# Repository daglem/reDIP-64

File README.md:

# reDIP 64

## Commodore 64 FPGA emulation platform

## Overview

The reDIP 64 is an open source hardware development board which
combines the following in a tiny 25.40 x 50.80 mm footprint:

* Lattice ECP5-5G FPGA (LFE5UM5G-25)
* NXP PTN5110NHQ USB PD TCPC PHY
* NXP SGTL5000 Audio Codec
* 128Mbit FLASH
* 128Mbit HyperRAM
* RGB LED
* Push button
* USB-C receptacle for power, Full Speed USB, and DisplayPort (DP Alt Mode)
* Lots of 5V tolerant I/O

The reDIP 64 aims at functioning as

* A partial or full brain transplant for the venerable Commodore 64
* A "Retro computer on a chip", which can be used stand-alone or in
  custom retro computer builds
* A versatile generic FPGA platform with power, HID input, and audio /
  video output all handled through a single USB-C connector

Designs for the ECP5 FPGA can be processed by
[yosys](https://github.com/YosysHQ/yosys/) and
[nextpnr](https://github.com/YosysHQ/nextpnr/).

Also check out the [reDIP SID](https://github.com/daglem/reDIP-SID),
if you are interested in a platform for MOS 6581 / 8580 SID emulation
in particular.

## General use

### I/O interfaces

#### 100 header pins:

* 5V input / output
* 3.3V output
* 92 FPGA GPIO
* 5 audio pins (stereo line input, stereo line output, GND)
* GND

All FPGA I/O is 5V tolerant, and can drive 5V TTL.

Note that the audio line inputs are not AC coupled - AC coupling must
be externally added for audio applications. Without external AC
coupling, the line inputs can conceivably be used as generic ADCs.

#### JTAG:

A separate 6 pin header is provided for JTAG.

#### USB-C functions:

* 5V power in / out
* USB Power Delivery (PD)
* FPGA Full Speed USB
* FPGA DisplayPort (DP Alt Mode)

## Commodore 64 compatibility

The board is pin compatible with the MOS 6510 / 8500 MPU chip, and has
additional pin headers to cover all the custom chips and I/O in the
Commodore 64:

* 6510 / 8500 MPU
* 6567/6569 / 8562/8565 VIC-II
* 6581 / 8580 SID (x 2)
* 2 x 6526 CIA
* Cartridge port signals
* Menu / freeze button

For anyone interested in experimenting with a Commodore 64 setup,
while avoiding blown fuses and a broken reDIP 64 board:

* A 2A C64 power supply is recommended
* Be careful not to apply force to SMD components on insertion and removal - use a ZIF socket if possible

The idea is that one can start by mounting the reDIP 64 in a Commodore
64, replacing the 6510 / 8500 MPU. This will make it possible to communicate
with the Commodore 64 via USB, to output audio and video via the USB-C
connector (DP Alt Mode), and to emulate a second SID chip.

Then, if one wishes to replace the VIC-II, the SID, or a CIA chip, the
custom chip is removed, and wires are run from the reDIP 64 to the
corresponding socket pins for the custom chip.

Note that the audio line outputs cannot drive the C64 audio output
stage directly, however an audio output may be connected directly to
pin 3 of the C64 audio/video connector (preferably removing or cutting
a pin on C13 in the C64).

Also note that unless suggested GPIO is repurposed for other
functions, the VIC-II can only be replaced by additionally emulating
all RAM chips, and the PLA can only be replaced by emulating *all*
custom chips, including ROM and RAM.

The MOS 8502 MPU used in the Commodore C128 has a similar pinout to
the MOS 6510. Since the same pins are used for power, the reDIP 64 can
conceivably also be used in a C128.

## Retro computer on a chip

Power, HID input, and audio / video can all be handled via the USB-C
port, hence the reDIP 64 is in fact capable of operating as a retro
computer all on its own. Just connect the reDIP 64 to a DisplayPort
monitor, either directly or via an USB hub, and add a keyboard and any
other HID input devices. Now, all that is needed is an FPGA
implementation of a retro computer :wink:

To create a fully functional retro computer, i.e. with I/O which can
interface with original perhiperals, physical connectors and glue
logic must be added to the mix. This can make for some fun projects!

Using the suggested GPIO, a fully functional custom C64 can be built
using a minimum of additional components.

## Other FPGA projects

The board can be of course also be used to experiment with e.g.

* DisplayPort audio / video
* Analog audio
* USB Power Delivery
* Interfacing with 5V TTL
* RISC-V and other CPU architectures
* Other SoC projects

## Disclaimer

Please note that this is only my third board design - rookie mistakes
are probably made, and feedback is welcome.

## Board images

Board Front | Board Back
----------- | ----------
 |

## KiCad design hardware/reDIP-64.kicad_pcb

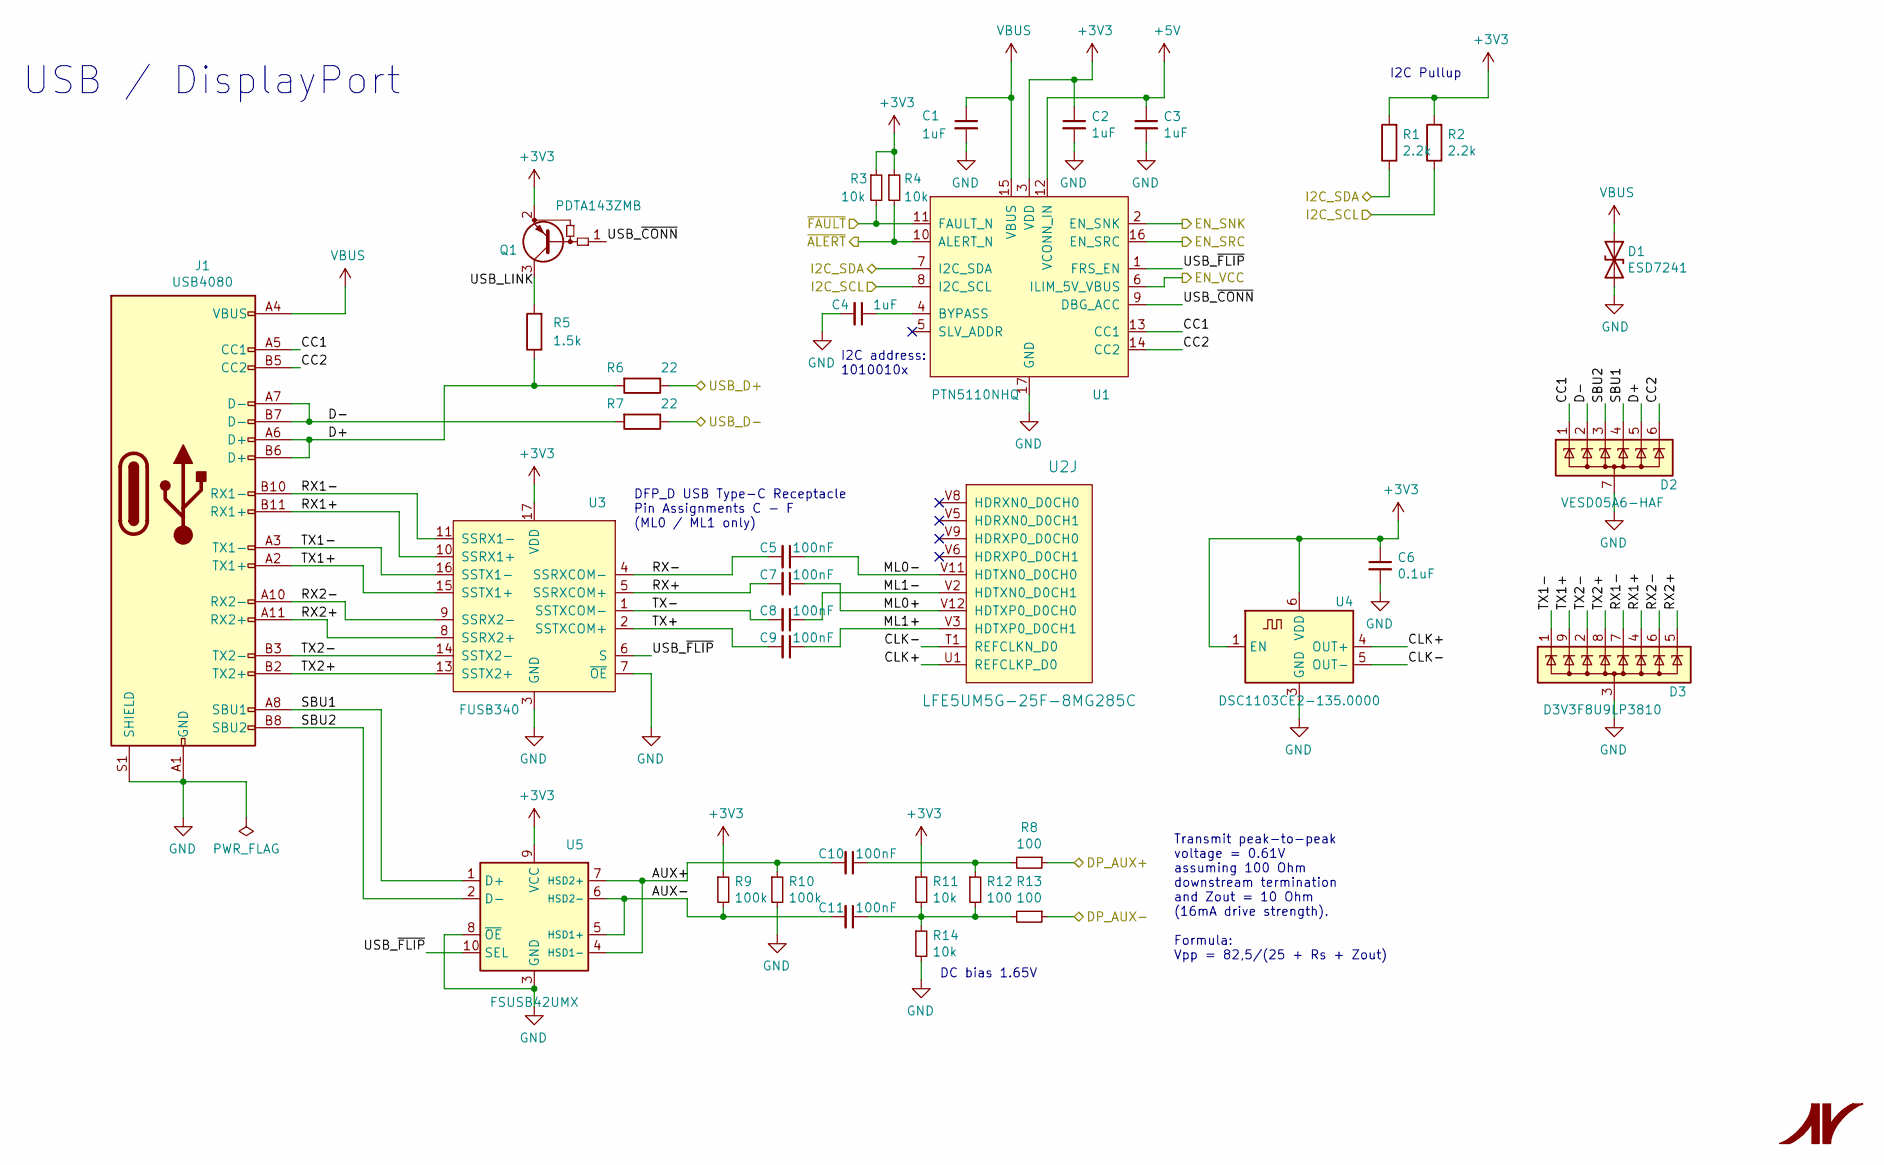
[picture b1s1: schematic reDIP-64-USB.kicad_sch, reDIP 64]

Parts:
C1: 1uF; C_0402_1005Metric
C2, C3, C4: 1uF; C_0201_0603Metric
C5, C7, C8, C9, C10, C11: 100nF; C_0201_0603Metric
C6: 0.1uF; C_0201_0603Metric
D1: ESD7241; CASE_714AB_1.0x0.6mm
D2: VESD05A6-HAF; LLP75-7L
D3: D3V3F8U9LP3810; U-DFN3810-9
J1: USB4080; USB_C_Receptacle_GCT_USB4080
Q1: PDTA143ZMB; SOT-883
R1, R2: 2.2k; R_0201_0603Metric
R3, R4, R11, R14: 10k; R_0201_0603Metric
R5: 1.5k; R_0201_0603Metric
R6, R7: 22; R_0201_0603Metric
R8, R12, R13: 100; R_0201_0603Metric
R9, R10: 100k; R_0201_0603Metric
U1: PTN5110NHQ; SOT-1883-1
U2: LFE5UM5G-25F-8MG285C; BGA-285_10x10mm_P0.5mm
U3: FUSB340; CASE_722AB_2.0x2.8mm_P0.4mm
U4: DSC1103CE2-135.0000; Oscillator_SMD_3225-6Pin_3.2x2.5mm
U5: FSUSB42UMX; CASE_523BC_1.4x1.8_P0.4mm

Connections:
+3V3: C2.1, C6.1, Q1.2 (E), R1.2, R2.2, R3.1, R4.1, R9.1, R11.1, U1.3 (VDD), U3.17 (VDD), U4.1 (EN), U4.6 (VDD), U5.9 (VCC); also elsewhere on the board
+5V: C3.1, U1.12 (VCONN_IN); also elsewhere on the board
/Audio/I2C_SCL: R2.1, U1.8 (I2C_SCL); also elsewhere on the board
/Audio/I2C_SDA: R1.1, U1.7 (I2C_SDA); also elsewhere on the board
/FPGA_IO/DP_AUX+: R8.1; also elsewhere on the board
/FPGA_IO/DP_AUX-: R13.1; also elsewhere on the board
/FPGA_IO/USB_D+: R6.1; also elsewhere on the board
/FPGA_IO/USB_D-: R7.1; also elsewhere on the board
/FPGA_IO/~ALERT: R4.2, U1.10 (ALERT_N); also elsewhere on the board
/Power/EN_SNK: U1.2 (EN_SNK); also elsewhere on the board
/Power/EN_SRC: U1.16 (EN_SRC); also elsewhere on the board
/Power/EN_VCC: U1.6 (ILIM_5V_VBUS); also elsewhere on the board
/Power/~FAULT: R3.2, U1.11 (FAULT_N); also elsewhere on the board
/USB_DisplayPort/AUX+: C10.2, R10.1, U5.4 (HSD1-), U5.7 (HSD2+)
/USB_DisplayPort/AUX-: C11.2, R9.2, U5.5 (HSD1+), U5.6 (HSD2-)
/USB_DisplayPort/CC1: D2.1 (K), J1.A5 (CC1), U1.13 (CC1)
/USB_DisplayPort/CC2: D2.6 (K), J1.B5 (CC2), U1.14 (CC2)
/USB_DisplayPort/CLK+: U2.U1 (REFCLKP_D0), U4.4 (OUT+)
/USB_DisplayPort/CLK-: U2.T1 (REFCLKN_D0), U4.5 (OUT-)
/USB_DisplayPort/D+: D2.5 (K), J1.A6 (D+), J1.B6 (D+), R5.1, R6.2
/USB_DisplayPort/D-: D2.2 (K), J1.A7 (D-), J1.B7 (D-), R7.2
/USB_DisplayPort/ML0+: C7.1, U2.V12 (HDTXP0_D0CH0)
/USB_DisplayPort/ML0-: C5.1, U2.V11 (HDTXN0_D0CH0)
/USB_DisplayPort/ML1+: C9.1, U2.V3 (HDTXP0_D0CH1)
/USB_DisplayPort/ML1-: C8.1, U2.V2 (HDTXN0_D0CH1)
/USB_DisplayPort/RX1+: D3.4 (Line-6), J1.B11 (RX1+), U3.10 (SSRX1+)
/USB_DisplayPort/RX1-: D3.7 (Line-5), J1.B10 (RX1-), U3.11 (SSRX1-)
/USB_DisplayPort/RX2+: D3.5 (Line-8), J1.A11 (RX2+), U3.8 (SSRX2+)
/USB_DisplayPort/RX2-: D3.6 (Line-7), J1.A10 (RX2-), U3.9 (SSRX2-)
/USB_DisplayPort/RX+: C7.2, U3.5 (SSRXCOM+)
/USB_DisplayPort/RX-: C5.2, U3.4 (SSRXCOM-)
/USB_DisplayPort/SBU1: D2.4 (K), J1.A8 (SBU1), U5.1 (D+)
/USB_DisplayPort/SBU2: D2.3 (K), J1.B8 (SBU2), U5.2 (D-)
/USB_DisplayPort/TX1+: D3.9 (Line-2), J1.A2 (TX1+), U3.15 (SSTX1+)
/USB_DisplayPort/TX1-: D3.1 (Line-1), J1.A3 (TX1-), U3.16 (SSTX1-)
/USB_DisplayPort/TX2+: D3.8 (Line-4), J1.B2 (TX2+), U3.13 (SSTX2+)
/USB_DisplayPort/TX2-: D3.2 (Line-3), J1.B3 (TX2-), U3.14 (SSTX2-)
/USB_DisplayPort/TX+: C9.2, U3.2 (SSTXCOM+)
/USB_DisplayPort/TX-: C8.2, U3.1 (SSTXCOM-)
/USB_DisplayPort/USB_LINK: Q1.3 (C), R5.2
/USB_DisplayPort/USB_~CONN: Q1.1 (B), U1.9 (DBG_ACC)
/USB_DisplayPort/USB_~FLIP: U1.1 (FRS_EN), U3.6 (S), U5.10 (SEL)
GND: C1.2, C2.2, C3.2, C4.2, C6.2, D1.2 (A2), D2.7 (GND), D3.3 (GND), J1.A1 (GND), J1.A12 (GND), J1.B1 (GND), J1.B12 (GND), J1.S1 (SHIELD), R10.2, R14.2, U1.17 (GND), U3.3 (GND), U3.7 (~OE), U3.12 (GND), U3.18 (GND), U3.19 (GND), U4.3 (GND), U5.3 (GND), U5.8 (~OE); also elsewhere on the board
unnamed: C10.1, R8.2, R12.1
unnamed: C11.1, R11.2, R12.2, R13.2, R14.1
unnamed: C4.1, U1.4 (BYPASS)
VBUS: C1.1, D1.1 (A1), J1.A4 (VBUS), J1.A9 (VBUS), J1.B4 (VBUS), J1.B9 (VBUS), U1.15 (VBUS); also elsewhere on the board

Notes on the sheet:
Transmit peak-to-peak voltage = 0.61V assuming 100 Ohm downstream termination and Zout = 10 Ohm (16mA drive strength). Formula: Vpp = 82,5/(25 + Rs + Zout)
USB / DisplayPort
DFP_D USB Type-C Receptacle Pin Assignments C - F (ML0 / ML1 only)
DC bias 1.65V
I2C address: 1010010x
I2C Pullup

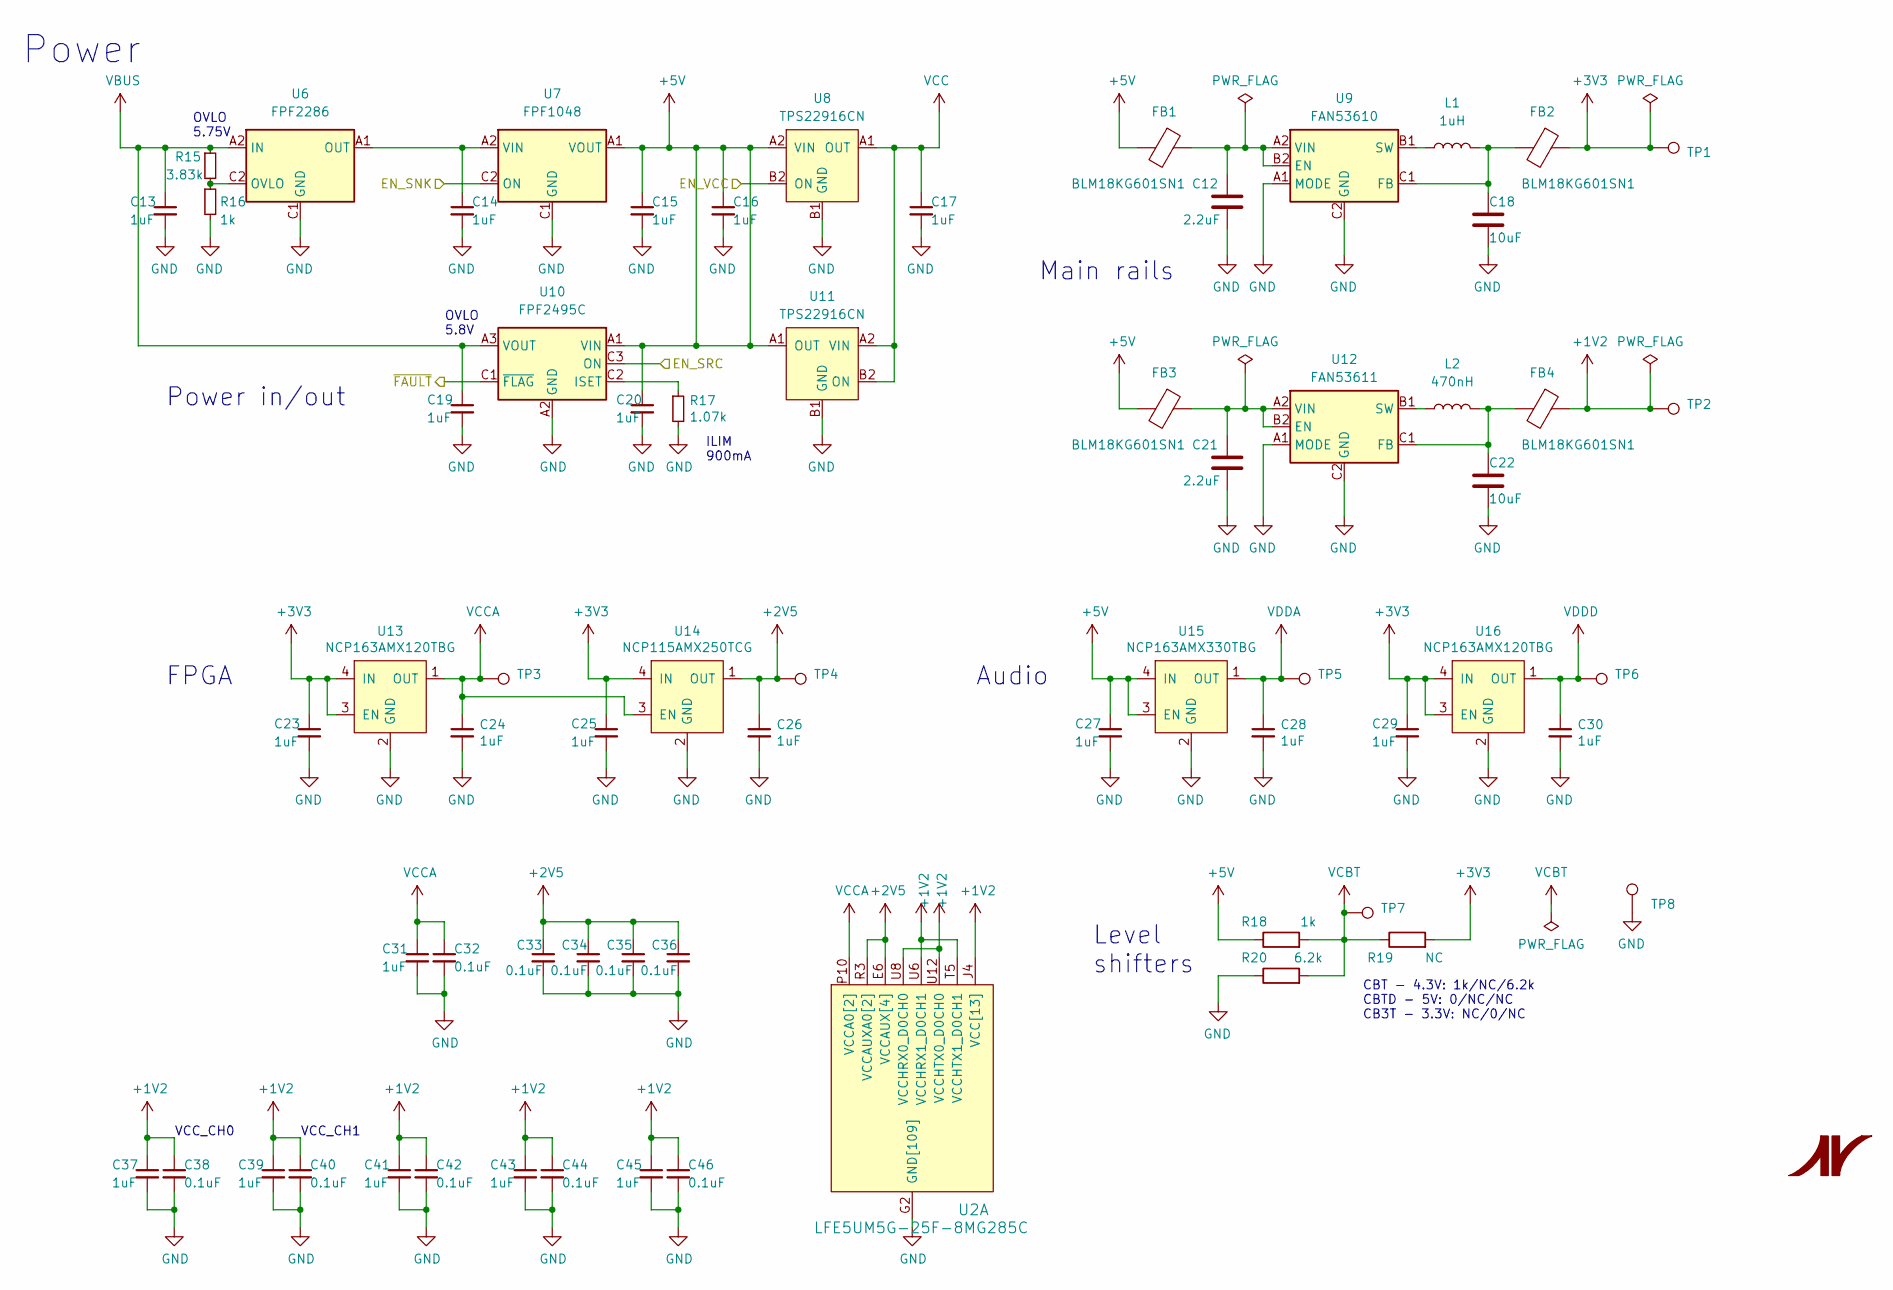
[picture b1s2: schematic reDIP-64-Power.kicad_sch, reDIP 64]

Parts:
C12, C21: 2.2uF; C_0402_1005Metric
C13, C14, C15, C16, C17, C19, C20, C27: 1uF; C_0402_1005Metric
C18: 10uF; C_0603_1608Metric
C22: 10uF; C_0402_1005Metric
C23, C24, C25, C26, C28, C29, C30, C31, C37, C39, C41, C43, C45: 1uF; C_0201_0603Metric
C32, C33, C34, C35, C36, C38, C40, C42, C44, C46: 0.1uF; C_0201_0603Metric
FB1, FB2, FB3, FB4: BLM18KG601SN1; L_0603_1608Metric
L1: 1uH; L_0603_1608Metric
L2: 470nH; L_0603_1608Metric
R15: 3.83k; R_0201_0603Metric
R16, R18: 1k; R_0201_0603Metric
R17: 1.07k; R_0201_0603Metric
R19: NC; R_0201_0603Metric
R20: 6.2k; R_0201_0603Metric
TP1, TP2, TP3, TP4, TP5, TP6, TP7, TP8: TestPoint; TestPoint_Pad_D0.5mm
U2: LFE5UM5G-25F-8MG285C; BGA-285_10x10mm_P0.5mm
U6: FPF2286; CASE_567UV_1.30x0.90mm_P0.4mm
U7: FPF1048; CASE_567RM_1.46x0.96mm_P0.5mm
U8, U11: TPS22916CN; Texas_DSBGA-4_0.78x0.78mm_Layout2x2_P0.4mm
U9: FAN53610; CASE_567RQ_1.16x0.86mm_P0.4mm
U10: FPF2495C; CASE_567RV_1.21x1.21mm_P0.4mm
U12: FAN53611; CASE_567RQ_1.16x0.86mm_P0.4mm
U13, U16: NCP163AMX120TBG; CASE_711AJ_1.0x1.0mm_P0.65mm
U14: NCP115AMX250TCG; CASE_711AJ_1.0x1.0mm_P0.65mm
U15: NCP163AMX330TBG; CASE_711AJ_1.0x1.0mm_P0.65mm

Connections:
+1V2: C37.1, C38.1, C39.1, C40.1, C41.1, C42.1, C43.1, C44.1, C45.1, C46.1, FB4.1, TP2.1, U2.D8 (VCC[13]), U2.D9 (VCC[13]), U2.D10 (VCC[13]), U2.D11 (VCC[13]), U2.J4 (VCC[13]), U2.J5 (VCC[13]), U2.J14 (VCC[13]), U2.J15 (VCC[13]), U2.M4 (VCC[13]), U2.M15 (VCC[13]), U2.P7 (VCC[13]), U2.P9 (VCC[13]), U2.P11 (VCC[13]), U2.T5 (VCCHTX1_D0CH1), U2.U6 (VCCHRX1_D0CH1), U2.U8 (VCCHRX0_D0CH0), U2.U12 (VCCHTX0_D0CH0)
+2V5: C26.1, C33.1, C34.1, C35.1, C36.1, TP4.1, U2.E6 (VCCAUX[4]), U2.E13 (VCCAUX[4]), U2.N6 (VCCAUX[4]), U2.P5 (VCCAUXA0[2]), U2.P13 (VCCAUX[4]), U2.R3 (VCCAUXA0[2]), U14.1 (OUT)
+3V3: C23.1, C25.1, C29.1, FB2.1, R19.2, TP1.1, U13.3 (EN), U13.4 (IN), U14.4 (IN), U16.3 (EN), U16.4 (IN); also elsewhere on the board
+5V: C15.1, C16.1, C20.1, C27.1, FB1.2, FB3.2, R18.1, U7.A1 (VOUT), U7.B1 (VOUT), U8.A2 (VIN), U10.A1 (VIN), U10.B1 (VIN), U11.A1 (OUT), U15.3 (EN), U15.4 (IN); also elsewhere on the board
/Power/EN_SNK: U7.C2 (ON); also elsewhere on the board
/Power/EN_SRC: U10.C3 (ON); also elsewhere on the board
/Power/EN_VCC: U8.B2 (ON); also elsewhere on the board
/Power/~FAULT: U10.C1 (~FLAG); also elsewhere on the board
GND: C12.2, C13.2, C14.2, C15.2, C16.2, C17.2, C18.2, C19.2, C20.2, C21.2, C22.2, C23.2, C24.2, C25.2, C26.2, C27.2, C28.2, C29.2, C30.2, C31.2, C32.2, C33.2, C34.2, C35.2, C36.2, C37.2, C38.2, C39.2, C40.2, C41.2, C42.2, C43.2, C44.2, C45.2, C46.2, R16.2, R17.2, R20.1, TP8.1, U2.B3 (GND[109]), U2.B16 (GND[109]), U2.E5 (GND[109]), U2.E7 (GND[109]), U2.E8 (GND[109]), U2.E9 (GND[109]), U2.E10 (GND[109]), U2.E11 (GND[109]), U2.E12 (GND[109]), U2.E14 (GND[109]), U2.F5 (GND[109]), U2.F6 (GND[109]), U2.F7 (GND[109]), U2.F8 (GND[109]), U2.F9 (GND[109]), U2.F10 (GND[109]), U2.F11 (GND[109]), U2.F12 (GND[109]), U2.F13 (GND[109]), U2.F14 (GND[109]), U2.G2 (GND[109]), U2.G6 (GND[109]), U2.G7 (GND[109]), U2.G8 (GND[109]), U2.G9 (GND[109]), U2.G10 (GND[109]), U2.G11 (GND[109]), U2.G12 (GND[109]), U2.G13 (GND[109]), U2.G17 (GND[109]), U2.H6 (GND[109]), U2.H7 (GND[109]), U2.H8 (GND[109]), U2.H9 (GND[109]), U2.H10 (GND[109]), U2.H11 (GND[109]), U2.H12 (GND[109]), U2.H13 (GND[109]), U2.J6 (GND[109]), U2.J7 (GND[109]), U2.J8 (GND[109]), U2.J9 (GND[109]), U2.J10 (GND[109]), U2.J11 (GND[109]), U2.J12 (GND[109]), U2.J13 (GND[109]), U2.K5 (GND[109]), U2.K6 (GND[109]), U2.K7 (GND[109]), U2.K8 (GND[109]), U2.K9 (GND[109]), U2.K10 (GND[109]), U2.K11 (GND[109]), U2.K12 (GND[109]), U2.K13 (GND[109]), U2.K14 (GND[109]), U2.L2 (GND[109]), U2.L5 (GND[109]), U2.L6 (GND[109]), U2.L7 (GND[109]), U2.L8 (GND[109]), U2.L9 (GND[109]), U2.L10 (GND[109]), U2.L11 (GND[109]), U2.L12 (GND[109]), U2.L13 (GND[109]), U2.L14 (GND[109]), U2.L17 (GND[109]), U2.M6 (GND[109]), U2.M7 (GND[109]), U2.M8 (GND[109]), U2.M9 (GND[109]), U2.M10 (GND[109]), U2.M11 (GND[109]), U2.M12 (GND[109]), U2.M13 (GND[109]), U2.N7 (GND[109]), U2.N8 (GND[109]), U2.N9 (GND[109]), U2.N10 (GND[109]), U2.N11 (GND[109]), U2.N12 (GND[109]), U2.P6 (GND[109]), U2.P8 (GND[109]), U2.P12 (GND[109]), U2.R1 (GND[109]), U2.R2 (GND[109]), U2.T2 (GND[109]), U2.T3 (GND[109]), U2.T4 (GND[109]), U2.T6 (GND[109]), U2.T7 (GND[109]), U2.T8 (GND[109]), U2.T9 (GND[109]), U2.T10 (GND[109]), U2.T11 (GND[109]), U2.T12 (GND[109]), U2.T16 (GND[109]), U2.U2 (GND[109]), U2.U3 (GND[109]), U2.U4 (GND[109]), U2.U5 (GND[109]), U2.U7 (GND[109]), U2.U9 (GND[109]), U2.U10 (GND[109]), U2.U11 (GND[109]), U2.V4 (GND[109]), U2.V7 (GND[109]), U2.V10 (GND[109]), U6.C1 (GND), U7.C1 (GND), U8.B1 (GND), U9.A1 (MODE), U9.C2 (GND), U10.A2 (GND), U10.B2 (GND), U11.B1 (GND), U12.A1 (MODE), U12.C2 (GND), U13.2 (GND), U14.2 (GND), U15.2 (GND), U16.2 (GND); also elsewhere on the board
unnamed: C14.1, U6.A1 (OUT), U6.B1 (OUT), U7.A2 (VIN), U7.B2 (VIN)
unnamed: R15.2, R16.1, U6.C2 (OVLO)
unnamed: C12.1, FB1.1, U9.A2 (VIN), U9.B2 (EN)
unnamed: C18.1, FB2.2, L1.2, U9.C1 (FB)
unnamed: L1.1, U9.B1 (SW)
unnamed: R17.1, U10.C2 (ISET)
unnamed: C21.1, FB3.1, U12.A2 (VIN), U12.B2 (EN)
unnamed: C22.1, FB4.2, L2.2, U12.C1 (FB)
unnamed: L2.1, U12.B1 (SW)
VBUS: C13.1, C19.1, R15.1, U6.A2 (IN), U6.B2 (IN), U10.A3 (VOUT), U10.B3 (VOUT); also elsewhere on the board
VCBT: R18.2, R19.1, R20.2, TP7.1; also elsewhere on the board
VCC: C17.1, U8.A1 (OUT), U11.A2 (VIN), U11.B2 (ON); also elsewhere on the board
VCCA: C24.1, C31.1, C32.1, TP3.1, U2.P10 (VCCA0[2]), U2.R10 (VCCA0[2]), U13.1 (OUT), U14.3 (EN)
VDDA: C28.1, TP5.1, U15.1 (OUT); also elsewhere on the board
VDDD: C30.1, TP6.1, U16.1 (OUT); also elsewhere on the board

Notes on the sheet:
OVLO 5.8V
Power
VCC_CH1
CBT - 4.3V: 1k/NC/6.2k CBTD - 5V: 0/NC/NC CB3T - 3.3V: NC/0/NC
OVLO 5.75V
ILIM 900mA
VCC_CH0
Power in/out
Audio
FPGA
Main rails
Level shifters

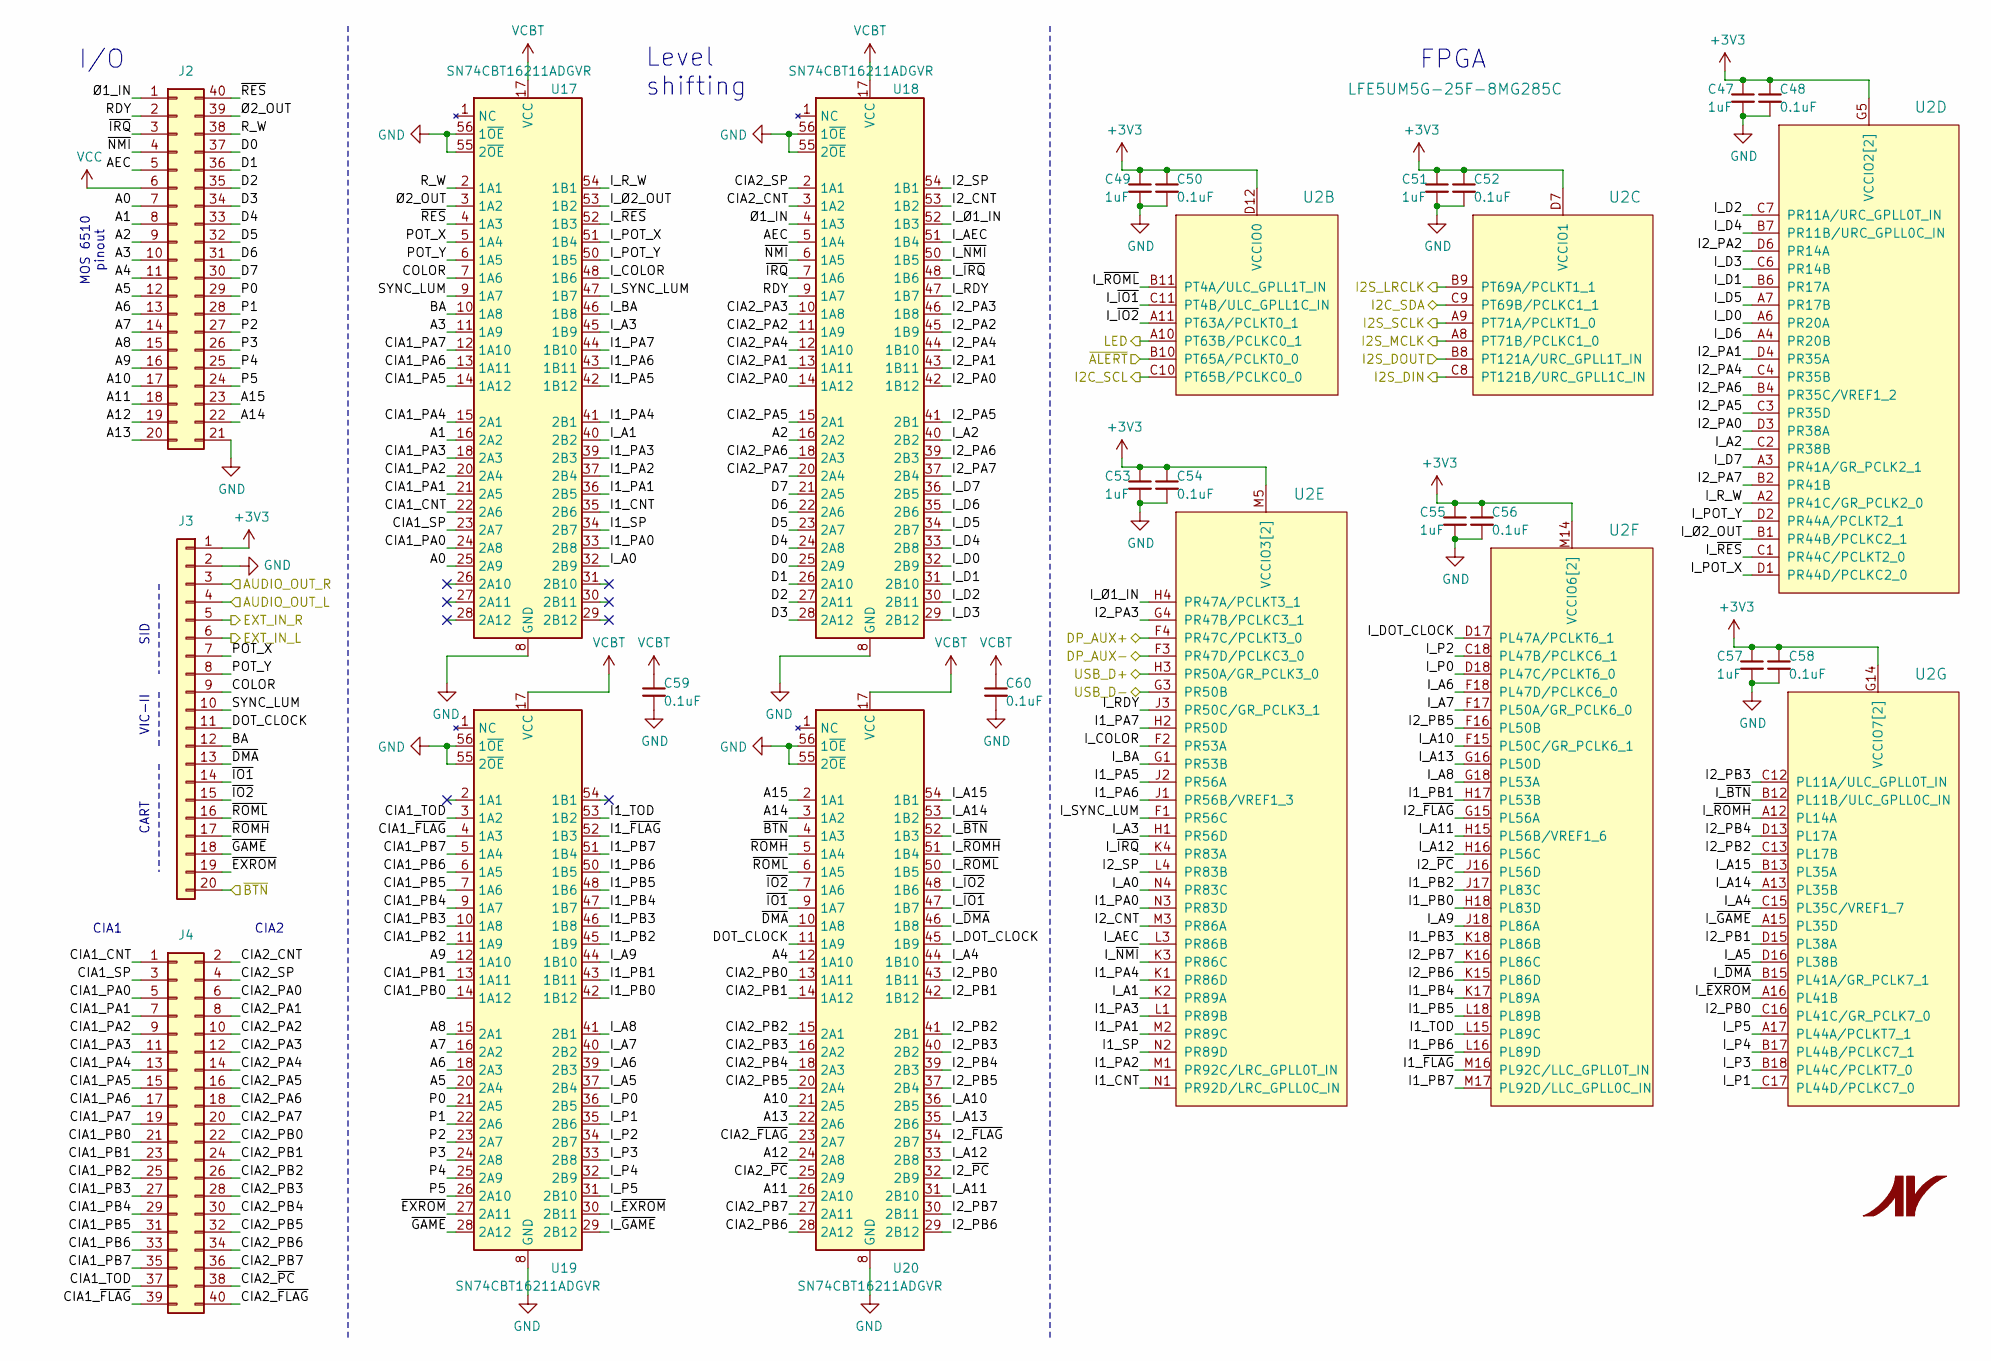
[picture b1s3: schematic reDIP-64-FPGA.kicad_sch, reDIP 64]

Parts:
C47, C49, C51, C53, C55, C57: 1uF; C_0201_0603Metric
C48, C50, C52, C54, C56, C58, C59, C60: 0.1uF; C_0201_0603Metric
J2: Conn_02x20_Counter_Clockwise; DIP-40_W15.24mm_Header
J3: Conn_01x20; PinHeader_1x20_P2.54mm_Vertical
J4: Conn_02x20_Odd_Even; PinHeader_2x20_P2.54mm_Vertical
U2: LFE5UM5G-25F-8MG285C; BGA-285_10x10mm_P0.5mm
U17, U18, U19, U20: SN74CBT16211ADGVR; Texas_TVSOP-56_4.4x11.3mm_P0.4mm

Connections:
+3V3: C47.1, C48.1, C49.1, C50.1, C51.1, C52.1, C53.1, C54.1, C55.1, C56.1, C57.1, C58.1, J3.1, U2.D7 (VCCIO1), U2.D12 (VCCIO0), U2.G5 (VCCIO2[2]), U2.G14 (VCCIO7[2]), U2.H5 (VCCIO2[2]), U2.H14 (VCCIO7[2]), U2.M5 (VCCIO3[2]), U2.M14 (VCCIO6[2]), U2.N5 (VCCIO3[2]), U2.N14 (VCCIO6[2]); also elsewhere on the board
/Audio/AUDIO_OUT_L: J3.4; also elsewhere on the board
/Audio/AUDIO_OUT_R: J3.3; also elsewhere on the board
/Audio/EXT_IN_L: J3.6; also elsewhere on the board
/Audio/EXT_IN_R: J3.5; also elsewhere on the board
/Audio/I2C_SCL: U2.C10 (PT65B/PCLKC0_0); also elsewhere on the board
/Audio/I2C_SDA: U2.C9 (PT69B/PCLKC1_1); also elsewhere on the board
/Audio/I2S_DIN: U2.C8 (PT121B/URC_GPLL1C_IN); also elsewhere on the board
/Audio/I2S_DOUT: U2.B8 (PT121A/URC_GPLL1T_IN); also elsewhere on the board
/Audio/I2S_LRCLK: U2.B9 (PT69A/PCLKT1_1); also elsewhere on the board
/Audio/I2S_MCLK: U2.A8 (PT71B/PCLKC1_0); also elsewhere on the board
/Audio/I2S_SCLK: U2.A9 (PT71A/PCLKT1_0); also elsewhere on the board
/Config_Memory/LED: U2.A10 (PT63B/PCLKC0_1); also elsewhere on the board
/FPGA_IO/A0: J2.7, U17.25 (2A9)
/FPGA_IO/A1: J2.8, U17.16 (2A2)
/FPGA_IO/A2: J2.9, U18.16 (2A2)
/FPGA_IO/A3: J2.10, U17.11 (1A9)
/FPGA_IO/A4: J2.11, U20.12 (1A10)
/FPGA_IO/A5: J2.12, U19.20 (2A4)
/FPGA_IO/A6: J2.13, U19.18 (2A3)
/FPGA_IO/A7: J2.14, U19.16 (2A2)
/FPGA_IO/A8: J2.15, U19.15 (2A1)
/FPGA_IO/A9: J2.16, U19.12 (1A10)
/FPGA_IO/A10: J2.17, U20.21 (2A5)
/FPGA_IO/A11: J2.18, U20.26 (2A10)
/FPGA_IO/A12: J2.19, U20.24 (2A8)
/FPGA_IO/A13: J2.20, U20.22 (2A6)
/FPGA_IO/A14: J2.22, U20.3 (1A2)
/FPGA_IO/A15: J2.23, U20.2 (1A1)
/FPGA_IO/AEC: J2.5, U18.5 (1A4)
/FPGA_IO/BA: J3.12, U17.10 (1A8)
/FPGA_IO/CIA1_CNT: J4.1, U17.22 (2A6)
/FPGA_IO/CIA1_PA0: J4.5, U17.24 (2A8)
/FPGA_IO/CIA1_PA1: J4.7, U17.21 (2A5)
/FPGA_IO/CIA1_PA2: J4.9, U17.20 (2A4)
/FPGA_IO/CIA1_PA3: J4.11, U17.18 (2A3)
/FPGA_IO/CIA1_PA4: J4.13, U17.15 (2A1)
/FPGA_IO/CIA1_PA5: J4.15, U17.14 (1A12)
/FPGA_IO/CIA1_PA6: J4.17, U17.13 (1A11)
/FPGA_IO/CIA1_PA7: J4.19, U17.12 (1A10)
/FPGA_IO/CIA1_PB0: J4.21, U19.14 (1A12)
/FPGA_IO/CIA1_PB1: J4.23, U19.13 (1A11)
/FPGA_IO/CIA1_PB2: J4.25, U19.11 (1A9)
/FPGA_IO/CIA1_PB3: J4.27, U19.10 (1A8)
/FPGA_IO/CIA1_PB4: J4.29, U19.9 (1A7)
/FPGA_IO/CIA1_PB5: J4.31, U19.7 (1A6)
/FPGA_IO/CIA1_PB6: J4.33, U19.6 (1A5)
/FPGA_IO/CIA1_PB7: J4.35, U19.5 (1A4)
/FPGA_IO/CIA1_SP: J4.3, U17.23 (2A7)
/FPGA_IO/CIA1_TOD: J4.37, U19.3 (1A2)
/FPGA_IO/CIA1_~FLAG: J4.39, U19.4 (1A3)
/FPGA_IO/CIA2_CNT: J4.2, U18.3 (1A2)
/FPGA_IO/CIA2_PA0: J4.6, U18.14 (1A12)
/FPGA_IO/CIA2_PA1: J4.8, U18.13 (1A11)
/FPGA_IO/CIA2_PA2: J4.10, U18.11 (1A9)
/FPGA_IO/CIA2_PA3: J4.12, U18.10 (1A8)
/FPGA_IO/CIA2_PA4: J4.14, U18.12 (1A10)
/FPGA_IO/CIA2_PA5: J4.16, U18.15 (2A1)
/FPGA_IO/CIA2_PA6: J4.18, U18.18 (2A3)
/FPGA_IO/CIA2_PA7: J4.20, U18.20 (2A4)
/FPGA_IO/CIA2_PB0: J4.22, U20.13 (1A11)
/FPGA_IO/CIA2_PB1: J4.24, U20.14 (1A12)
/FPGA_IO/CIA2_PB2: J4.26, U20.15 (2A1)
/FPGA_IO/CIA2_PB3: J4.28, U20.16 (2A2)
/FPGA_IO/CIA2_PB4: J4.30, U20.18 (2A3)
/FPGA_IO/CIA2_PB5: J4.32, U20.20 (2A4)
/FPGA_IO/CIA2_PB6: J4.34, U20.28 (2A12)
/FPGA_IO/CIA2_PB7: J4.36, U20.27 (2A11)
/FPGA_IO/CIA2_SP: J4.4, U18.2 (1A1)
/FPGA_IO/CIA2_~FLAG: J4.40, U20.23 (2A7)
/FPGA_IO/CIA2_~PC: J4.38, U20.25 (2A9)
/FPGA_IO/COLOR: J3.9, U17.7 (1A6)
/FPGA_IO/D0: J2.37, U18.25 (2A9)
/FPGA_IO/D1: J2.36, U18.26 (2A10)
/FPGA_IO/D2: J2.35, U18.27 (2A11)
/FPGA_IO/D3: J2.34, U18.28 (2A12)
/FPGA_IO/D4: J2.33, U18.24 (2A8)
/FPGA_IO/D5: J2.32, U18.23 (2A7)
/FPGA_IO/D6: J2.31, U18.22 (2A6)
/FPGA_IO/D7: J2.30, U18.21 (2A5)
/FPGA_IO/DOT_CLOCK: J3.11, U20.11 (1A9)
/FPGA_IO/DP_AUX+: U2.F4 (PR47C/PCLKT3_0); also elsewhere on the board
/FPGA_IO/DP_AUX-: U2.F3 (PR47D/PCLKC3_0); also elsewhere on the board
/FPGA_IO/I1_CNT: U2.N1 (PR92D/LRC_GPLL0C_IN), U17.35 (2B6)
/FPGA_IO/I1_PA0: U2.N3 (PR83D), U17.33 (2B8)
/FPGA_IO/I1_PA1: U2.M2 (PR89C), U17.36 (2B5)
/FPGA_IO/I1_PA2: U2.M1 (PR92C/LRC_GPLL0T_IN), U17.37 (2B4)
/FPGA_IO/I1_PA3: U2.L1 (PR89B), U17.39 (2B3)
/FPGA_IO/I1_PA4: U2.K1 (PR86D), U17.41 (2B1)
/FPGA_IO/I1_PA5: U2.J2 (PR56A), U17.42 (1B12)
/FPGA_IO/I1_PA6: U2.J1 (PR56B/VREF1_3), U17.43 (1B11)
/FPGA_IO/I1_PA7: U2.H2 (PR50D), U17.44 (1B10)
/FPGA_IO/I1_PB0: U2.H18 (PL83D), U19.42 (1B12)
/FPGA_IO/I1_PB1: U2.H17 (PL53B), U19.43 (1B11)
/FPGA_IO/I1_PB2: U2.J17 (PL83C), U19.45 (1B9)
/FPGA_IO/I1_PB3: U2.K18 (PL86B), U19.46 (1B8)
/FPGA_IO/I1_PB4: U2.K17 (PL89A), U19.47 (1B7)
/FPGA_IO/I1_PB5: U2.L18 (PL89B), U19.48 (1B6)
/FPGA_IO/I1_PB6: U2.L16 (PL89D), U19.50 (1B5)
/FPGA_IO/I1_PB7: U2.M17 (PL92D/LLC_GPLL0C_IN), U19.51 (1B4)
/FPGA_IO/I1_SP: U2.N2 (PR89D), U17.34 (2B7)
/FPGA_IO/I1_TOD: U2.L15 (PL89C), U19.53 (1B2)
/FPGA_IO/I1_~FLAG: U2.M16 (PL92C/LLC_GPLL0T_IN), U19.52 (1B3)
/FPGA_IO/I2_CNT: U2.M3 (PR86A), U18.53 (1B2)
/FPGA_IO/I2_PA0: U2.D3 (PR38A), U18.42 (1B12)
/FPGA_IO/I2_PA1: U2.D4 (PR35A), U18.43 (1B11)
/FPGA_IO/I2_PA2: U2.D6 (PR14A), U18.45 (1B9)
/FPGA_IO/I2_PA3: U2.G4 (PR47B/PCLKC3_1), U18.46 (1B8)
/FPGA_IO/I2_PA4: U2.C4 (PR35B), U18.44 (1B10)
/FPGA_IO/I2_PA5: U2.C3 (PR35D), U18.41 (2B1)
/FPGA_IO/I2_PA6: U2.B4 (PR35C/VREF1_2), U18.39 (2B3)
/FPGA_IO/I2_PA7: U2.B2 (PR41B), U18.37 (2B4)
/FPGA_IO/I2_PB0: U2.C16 (PL41C/GR_PCLK7_0), U20.43 (1B11)
/FPGA_IO/I2_PB1: U2.D15 (PL38A), U20.42 (1B12)
/FPGA_IO/I2_PB2: U2.C13 (PL17B), U20.41 (2B1)
/FPGA_IO/I2_PB3: U2.C12 (PL11A/ULC_GPLL0T_IN), U20.40 (2B2)
/FPGA_IO/I2_PB4: U2.D13 (PL17A), U20.39 (2B3)
/FPGA_IO/I2_PB5: U2.F16 (PL50B), U20.37 (2B4)
/FPGA_IO/I2_PB6: U2.K15 (PL86D), U20.29 (2B12)
/FPGA_IO/I2_PB7: U2.K16 (PL86C), U20.30 (2B11)
/FPGA_IO/I2_SP: U2.L4 (PR83B), U18.54 (1B1)
/FPGA_IO/I2_~FLAG: U2.G15 (PL56A), U20.34 (2B7)
/FPGA_IO/I2_~PC: U2.J16 (PL56D), U20.32 (2B9)
/FPGA_IO/I_A0: U2.N4 (PR83C), U17.32 (2B9)
/FPGA_IO/I_A1: U2.K2 (PR89A), U17.40 (2B2)
/FPGA_IO/I_A2: U2.C2 (PR38B), U18.40 (2B2)
/FPGA_IO/I_A3: U2.H1 (PR56D), U17.45 (1B9)
/FPGA_IO/I_A4: U2.C15 (PL35C/VREF1_7), U20.44 (1B10)
/FPGA_IO/I_A5: U2.D16 (PL38B), U19.37 (2B4)
/FPGA_IO/I_A6: U2.F18 (PL47D/PCLKC6_0), U19.39 (2B3)
/FPGA_IO/I_A7: U2.F17 (PL50A/GR_PCLK6_0), U19.40 (2B2)
/FPGA_IO/I_A8: U2.G18 (PL53A), U19.41 (2B1)
/FPGA_IO/I_A9: U2.J18 (PL86A), U19.44 (1B10)
/FPGA_IO/I_A10: U2.F15 (PL50C/GR_PCLK6_1), U20.36 (2B5)
/FPGA_IO/I_A11: U2.H15 (PL56B/VREF1_6), U20.31 (2B10)
/FPGA_IO/I_A12: U2.H16 (PL56C), U20.33 (2B8)
/FPGA_IO/I_A13: U2.G16 (PL50D), U20.35 (2B6)
/FPGA_IO/I_A14: U2.A13 (PL35B), U20.53 (1B2)
/FPGA_IO/I_A15: U2.B13 (PL35A), U20.54 (1B1)
/FPGA_IO/I_AEC: U2.L3 (PR86B), U18.51 (1B4)
/FPGA_IO/I_BA: U2.G1 (PR53B), U17.46 (1B8)
/FPGA_IO/I_COLOR: U2.F2 (PR53A), U17.48 (1B6)
/FPGA_IO/I_D0: U2.A6 (PR20A), U18.32 (2B9)
/FPGA_IO/I_D1: U2.B6 (PR17A), U18.31 (2B10)
/FPGA_IO/I_D2: U2.C7 (PR11A/URC_GPLL0T_IN), U18.30 (2B11)
/FPGA_IO/I_D3: U2.C6 (PR14B), U18.29 (2B12)
/FPGA_IO/I_D4: U2.B7 (PR11B/URC_GPLL0C_IN), U18.33 (2B8)
/FPGA_IO/I_D5: U2.A7 (PR17B), U18.34 (2B7)
/FPGA_IO/I_D6: U2.A4 (PR20B), U18.35 (2B6)
/FPGA_IO/I_D7: U2.A3 (PR41A/GR_PCLK2_1), U18.36 (2B5)
/FPGA_IO/I_DOT_CLOCK: U2.D17 (PL47A/PCLKT6_1), U20.45 (1B9)
/FPGA_IO/I_P0: U2.D18 (PL47C/PCLKT6_0), U19.36 (2B5)
/FPGA_IO/I_P1: U2.C17 (PL44D/PCLKC7_0), U19.35 (2B6)
/FPGA_IO/I_P2: U2.C18 (PL47B/PCLKC6_1), U19.34 (2B7)
/FPGA_IO/I_P3: U2.B18 (PL44C/PCLKT7_0), U19.33 (2B8)
/FPGA_IO/I_P4: U2.B17 (PL44B/PCLKC7_1), U19.32 (2B9)
/FPGA_IO/I_P5: U2.A17 (PL44A/PCLKT7_1), U19.31 (2B10)
/FPGA_IO/I_POT_X: U2.D1 (PR44D/PCLKC2_0), U17.51 (1B4)
/FPGA_IO/I_POT_Y: U2.D2 (PR44A/PCLKT2_1), U17.50 (1B5)
/FPGA_IO/I_RDY: U2.J3 (PR50C/GR_PCLK3_1), U18.47 (1B7)
/FPGA_IO/I_R_W: U2.A2 (PR41C/GR_PCLK2_0), U17.54 (1B1)
/FPGA_IO/I_SYNC_LUM: U2.F1 (PR56C), U17.47 (1B7)
/FPGA_IO/I_~BTN: U2.B12 (PL11B/ULC_GPLL0C_IN), U20.52 (1B3)
/FPGA_IO/I_~DMA: U2.B15 (PL41A/GR_PCLK7_1), U20.46 (1B8)
/FPGA_IO/I_~EXROM: U2.A16 (PL41B), U19.30 (2B11)
/FPGA_IO/I_~GAME: U2.A15 (PL35D), U19.29 (2B12)
/FPGA_IO/I_~IO1: U2.C11 (PT4B/ULC_GPLL1C_IN), U20.47 (1B7)
/FPGA_IO/I_~IO2: U2.A11 (PT63A/PCLKT0_1), U20.48 (1B6)
/FPGA_IO/I_~IRQ: U2.K4 (PR83A), U18.48 (1B6)
/FPGA_IO/I_~NMI: U2.K3 (PR86C), U18.50 (1B5)
/FPGA_IO/I_~RES: U2.C1 (PR44C/PCLKT2_0), U17.52 (1B3)
/FPGA_IO/I_~ROMH: U2.A12 (PL14A), U20.51 (1B4)
/FPGA_IO/I_~ROML: U2.B11 (PT4A/ULC_GPLL1T_IN), U20.50 (1B5)
/FPGA_IO/I_Ø1_IN: U2.H4 (PR47A/PCLKT3_1), U18.52 (1B3)
/FPGA_IO/I_Ø2_OUT: U2.B1 (PR44B/PCLKC2_1), U17.53 (1B2)
/FPGA_IO/P0: J2.29, U19.21 (2A5)
/FPGA_IO/P1: J2.28, U19.22 (2A6)
/FPGA_IO/P2: J2.27, U19.23 (2A7)
/FPGA_IO/P3: J2.26, U19.24 (2A8)
/FPGA_IO/P4: J2.25, U19.25 (2A9)
/FPGA_IO/P5: J2.24, U19.26 (2A10)
/FPGA_IO/POT_X: J3.7, U17.5 (1A4)
/FPGA_IO/POT_Y: J3.8, U17.6 (1A5)
/FPGA_IO/RDY: J2.2, U18.9 (1A7)
/FPGA_IO/R_W: J2.38, U17.2 (1A1)
/FPGA_IO/SYNC_LUM: J3.10, U17.9 (1A7)
/FPGA_IO/USB_D+: U2.H3 (PR50A/GR_PCLK3_0); also elsewhere on the board
/FPGA_IO/USB_D-: U2.G3 (PR50B); also elsewhere on the board
/FPGA_IO/~ALERT: U2.B10 (PT65A/PCLKT0_0); also elsewhere on the board
/FPGA_IO/~BTN: J3.20, U20.4 (1A3); also elsewhere on the board
/FPGA_IO/~DMA: J3.13, U20.10 (1A8)
/FPGA_IO/~EXROM: J3.19, U19.27 (2A11)
/FPGA_IO/~GAME: J3.18, U19.28 (2A12)
/FPGA_IO/~IO1: J3.14, U20.9 (1A7)
/FPGA_IO/~IO2: J3.15, U20.7 (1A6)
/FPGA_IO/~IRQ: J2.3, U18.7 (1A6)
/FPGA_IO/~NMI: J2.4, U18.6 (1A5)
/FPGA_IO/~RES: J2.40, U17.4 (1A3)
/FPGA_IO/~ROMH: J3.17, U20.5 (1A4)
/FPGA_IO/~ROML: J3.16, U20.6 (1A5)
/FPGA_IO/Ø1_IN: J2.1, U18.4 (1A3)
/FPGA_IO/Ø2_OUT: J2.39, U17.3 (1A2)
GND: C47.2, C48.2, C49.2, C50.2, C51.2, C52.2, C53.2, C54.2, C55.2, C56.2, C57.2, C58.2, C59.2, C60.2, J2.21, J3.2, U17.8 (GND), U17.19 (GND), U17.38 (GND), U17.49 (GND), U17.55 (2~OE), U17.56 (1~OE), U18.8 (GND), U18.19 (GND), U18.38 (GND), U18.49 (GND), U18.55 (2~OE), U18.56 (1~OE), U19.8 (GND), U19.19 (GND), U19.38 (GND), U19.49 (GND), U19.55 (2~OE), U19.56 (1~OE), U20.8 (GND), U20.19 (GND), U20.38 (GND), U20.49 (GND), U20.55 (2~OE), U20.56 (1~OE); also elsewhere on the board
VCBT: C59.1, C60.1, U17.17 (VCC), U18.17 (VCC), U19.17 (VCC), U20.17 (VCC); also elsewhere on the board
VCC: J2.6; also elsewhere on the board

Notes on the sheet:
VIC-II
CIA1
FPGA
I/O
MOS 6510 pinout
SID
CIA2
CART
Level shifting

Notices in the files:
hardware/reDIP-64-Audio.kicad_sch:
© 2021-2022 Dag Lem
Licensed under CERN-OHL-S v2 (https://ohwr.org/cern_ohl_s_v2.txt)
hardware/reDIP-64.kicad_pcb:
CERN-OHL-S v2
© 2022 Dag Lem
